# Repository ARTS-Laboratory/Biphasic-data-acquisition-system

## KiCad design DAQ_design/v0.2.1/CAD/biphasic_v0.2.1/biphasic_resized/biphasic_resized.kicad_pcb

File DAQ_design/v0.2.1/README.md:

# V0.2.1
All the files and soruce code developed by Borke at the University of Perugia

This version was transfered to KiCAD 7.0.2 and some changes where made. 

Added Arduino Nano interface and removed ATMega mandatories (clock, usb, etc.)

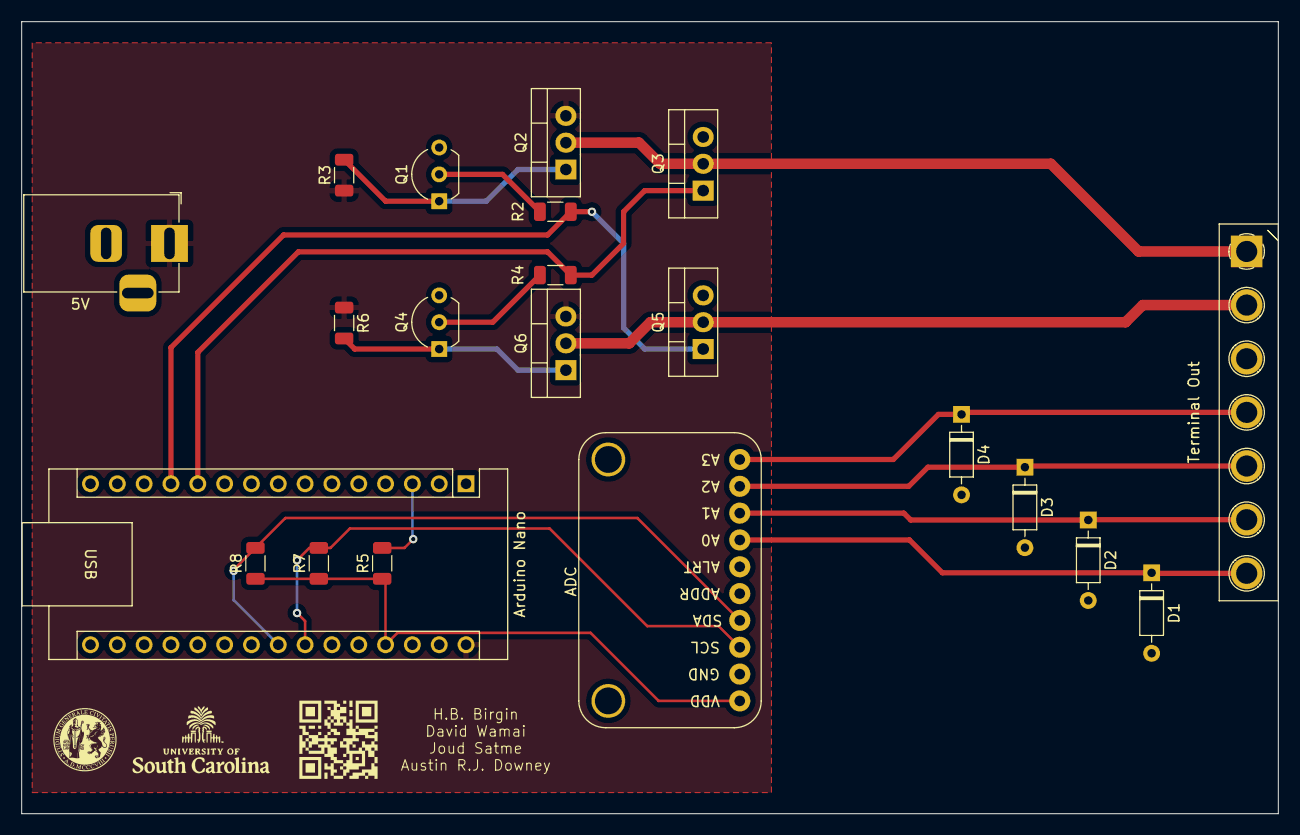
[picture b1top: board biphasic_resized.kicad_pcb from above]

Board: 2 copper layers, 119.0 x 75.0 mm, 25 parts (1 on the bottom side), 18 nets.

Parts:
5V: Barrel_Jack; BarrelJack_Horizontal
ADC: ADS1115IDGS; Adafruit_ADS1115
Arduino Nano: Arduino_Nano_Every; Arduino_Nano
D1, D2, D3, D4: D_Zener; D_DO-35_SOD27_P7.62mm_Horizontal
G2: LOGO; uofsc
G3: LOGO; upg
G5: LOGO; schematic
G7: LOGO; github
Q1, Q4: BC549; TO-92_Inline_Wide
Q2, Q6: IRF9540N; TO-220-3_Vertical
Q3, Q5: IRF540N; TO-220-3_Vertical
R2, R4: 1k; R_1206_3216Metric
R3, R5, R6, R7, R8: 10k; R_1206_3216Metric
Terminal Out: Screw_Terminal_01x07; TerminalBlock_Phoenix_MKDS-1,5-7-5.08_1x07_P5.08mm_Horizont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

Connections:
AIN0: ADC.7 (AIN0), D1.1 (K), Terminal Out.7
AIN1: ADC.8 (AIN1), D2.1 (K), Terminal Out.6
AIN2: ADC.9 (AIN2), D3.1 (K), Terminal Out.5
AIN3: ADC.10 (AIN3), D4.1 (K), Terminal Out.4
GND: 5V.2, ADC.2 (GND), ADC.5 (ADDR), Arduino Nano.4 (GND), Arduino Nano.29 (GND), D1.2 (A), D2.2 (A), D3.2 (A), D4.2 (A), Q1.3 (E), Q3.3 (S), Q4.3 (E), Q5.3 (S), Terminal Out.3
LOGIC1: Arduino Nano.12 (D9), Q5.1 (G), R2.2
LOGIC2: Arduino Nano.11 (D8), Q3.1 (G), R4.2
unnamed: ADC.3 (SCL), Arduino Nano.24 (SCL/A5), R7.2
unnamed: ADC.4 (SDA), Arduino Nano.23 (SDA/A4), R8.2
unnamed: Arduino Nano.3 (~RESET), R5.2
unnamed: Q1.2 (B), R2.1
unnamed: Q1.1 (C), Q2.1 (G), R3.2
unnamed: Q4.2 (B), R4.1
unnamed: Q4.1 (C), Q6.1 (G), R6.2
SN: Q5.2 (D), Q6.2 (D), Terminal Out.2
SP: Q2.2 (D), Q3.2 (D), Terminal Out.1
VDD: ADC.1 (VDD), Arduino Nano.27 (+5V), R5.1, R7.1, R8.1
VPP: 5V.1, Arduino Nano.30 (VIN), Q2.3 (S), Q6.3 (S), R3.1, R6.1

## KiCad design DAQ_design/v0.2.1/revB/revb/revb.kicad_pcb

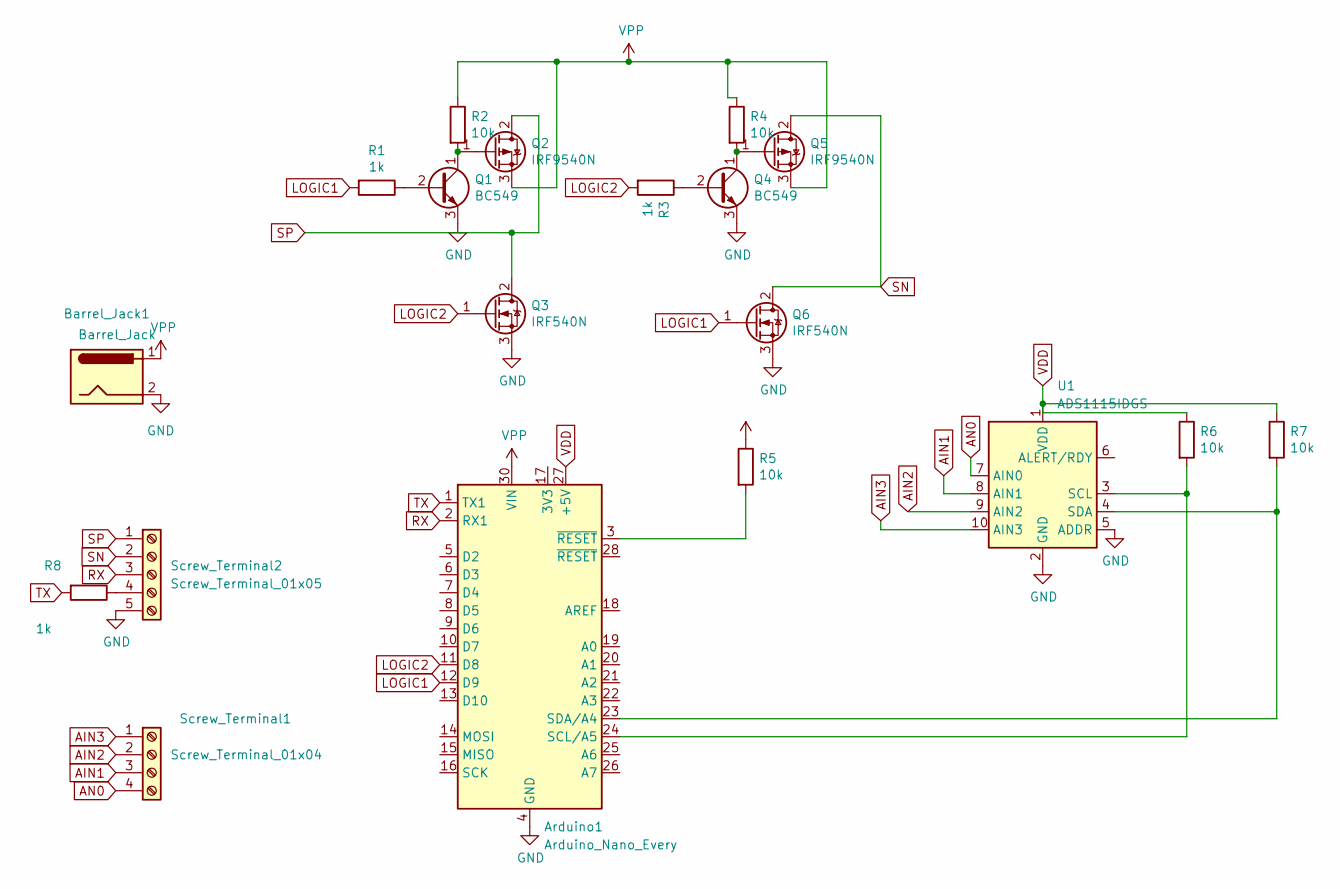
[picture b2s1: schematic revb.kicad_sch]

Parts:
Arduino1: Arduino_Nano_Every; Arduino_Nano_WithMountingHoles
Barrel_Jack1: Barrel_Jack; BarrelJack_Horizontal
Q1, Q4: BC549; TO-92_Inline_Wide
Q2, Q5: IRF9540N; TO-220-3_Vertical
Q3, Q6: IRF540N; TO-220-3_Vertical
R1, R3, R8: 1k; R_1206_3216Metric
R2, R4, R5, R6, R7: 10k; R_1206_3216Metric
Screw_Terminal1: Screw_Terminal_01x04; TerminalBlock_bornier-4_P5.08mm
Screw_Terminal2: Screw_Terminal_01x05; TerminalBlock_bornier-5_P5.08mm
U1: ADS1115IDGS; Adafruit_ADS1115

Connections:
AIN1: Screw_Terminal1.3, U1.8 (AIN1)
AIN2: Screw_Terminal1.2, U1.9 (AIN2)
AIN3: Screw_Terminal1.1, U1.10 (AIN3)
AN0: Screw_Terminal1.4, U1.7 (AIN0)
GND: Arduino1.4 (GND), Arduino1.29 (GND), Barrel_Jack1.2, Q1.3 (E), Q3.3 (S), Q4.3 (E), Q6.3 (S), Screw_Terminal2.5, U1.2 (GND), U1.5 (ADDR)
LOGIC1: Arduino1.12 (D9), Q6.1 (G), R1.2
LOGIC2: Arduino1.11 (D8), Q3.1 (G), R3.2
unnamed: Arduino1.24 (SCL/A5), R6.2, U1.3 (SCL)
unnamed: Arduino1.23 (SDA/A4), R7.2, U1.4 (SDA)
unnamed: Arduino1.3 (~RESET), R5.2
unnamed: Q1.2 (B), R1.1
unnamed: Q1.1 (C), Q2.1 (G), R2.2
unnamed: Q4.2 (B), R3.1
unnamed: Q4.1 (C), Q5.1 (G), R4.2
unnamed: R8.1, Screw_Terminal2.4
RX: Arduino1.2 (RX1), Screw_Terminal2.3
SN: Q5.2 (D), Q6.2 (D), Screw_Terminal2.2
SP: Q2.2 (D), Q3.2 (D), Screw_Terminal2.1
TX: Arduino1.1 (TX1), R8.2
VDD: Arduino1.27 (+5V), R5.1, R6.1, R7.1, U1.1 (VDD)
VPP: Arduino1.30 (VIN), Barrel_Jack1.1, Q2.3 (S), Q5.3 (S), R2.1, R4.1

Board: 2 copper layers, 23 parts (1 on the bottom side), 21 nets, no tracks yet.

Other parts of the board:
G2: LOGO; uofsc
G3: LOGO; upg
G5: LOGO; schematic
G7: LOGO; github

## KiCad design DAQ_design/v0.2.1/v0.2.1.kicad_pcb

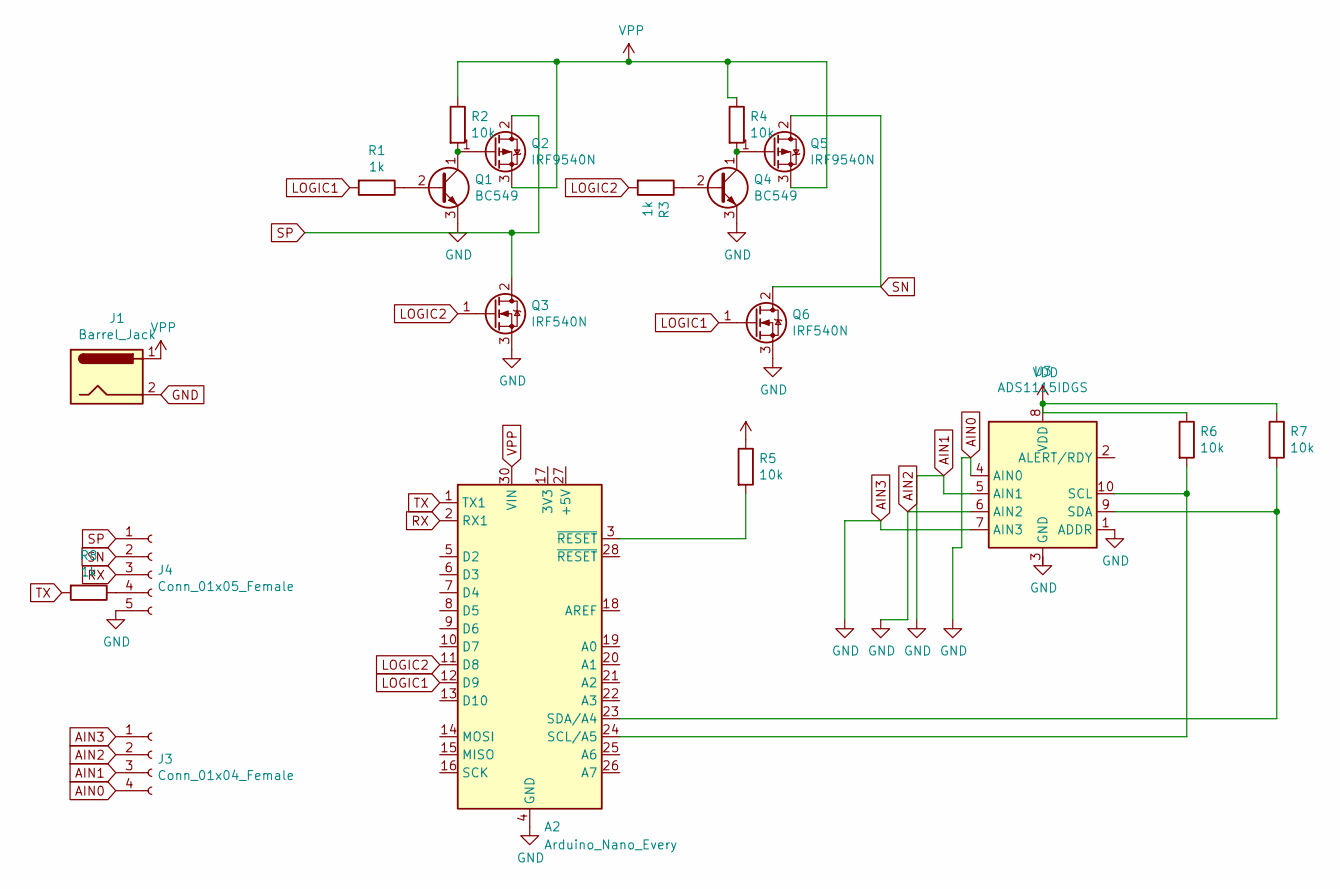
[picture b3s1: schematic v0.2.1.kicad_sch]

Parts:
A2: Arduino_Nano_Every; Arduino_Nano_WithMountingHoles
J1: Barrel_Jack; BarrelJack_Horizontal
J3: Conn_01x04_Female; PinSocket_1x04_P2.54mm_Vertical
J4: Conn_01x05_Female; PinSocket_1x05_P2.54mm_Vertical
Q1, Q4: BC549; TO-92_Inline_Wide
Q2, Q5: IRF9540N; TO-220-3_Vertical
Q3, Q6: IRF540N; TO-220-3_Vertical
R1, R3, R8: 1k; R_0603_1608Metric
R2, R4, R5, R6, R7: 10k; R_0603_1608Metric
U3: ADS1115IDGS; TSSOP-10_3x3mm_P0.5mm

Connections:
AIN0: A2.4 (GND), A2.29 (GND), J1.2, J3.1, J3.2, J3.3, J3.4, J4.5, Q1.3 (E), Q3.3 (S), Q4.3 (E), Q6.3 (S), U3.1 (ADDR), U3.4 (AIN0), U3.5 (AIN1), U3.6 (AIN2), U3.7 (AIN3)
LOGIC1: A2.12 (D9), Q6.1 (G), R1.2
LOGIC2: A2.11 (D8), Q3.1 (G), R3.2
unnamed: A2.24 (SCL/A5), R6.2, U3.10 (SCL)
unnamed: A2.23 (SDA/A4), R7.2, U3.9 (SDA)
unnamed: A2.3 (~RESET), R5.2
unnamed: J4.4, R8.1
unnamed: Q1.2 (B), R1.1
unnamed: Q1.1 (C), Q2.1 (G), R2.2
unnamed: Q4.2 (B), R3.1
unnamed: Q4.1 (C), Q5.1 (G), R4.2
RX: A2.2 (RX1), J4.3
SN: J4.2, Q5.2 (D), Q6.2 (D)
SP: J4.1, Q2.2 (D), Q3.2 (D)
TX: A2.1 (TX1), R8.2
VDD: R5.1, R6.1, R7.1, U3.8 (VDD)
VPP: A2.30 (VIN), J1.1, Q2.3 (S), Q5.3 (S), R2.1, R4.1

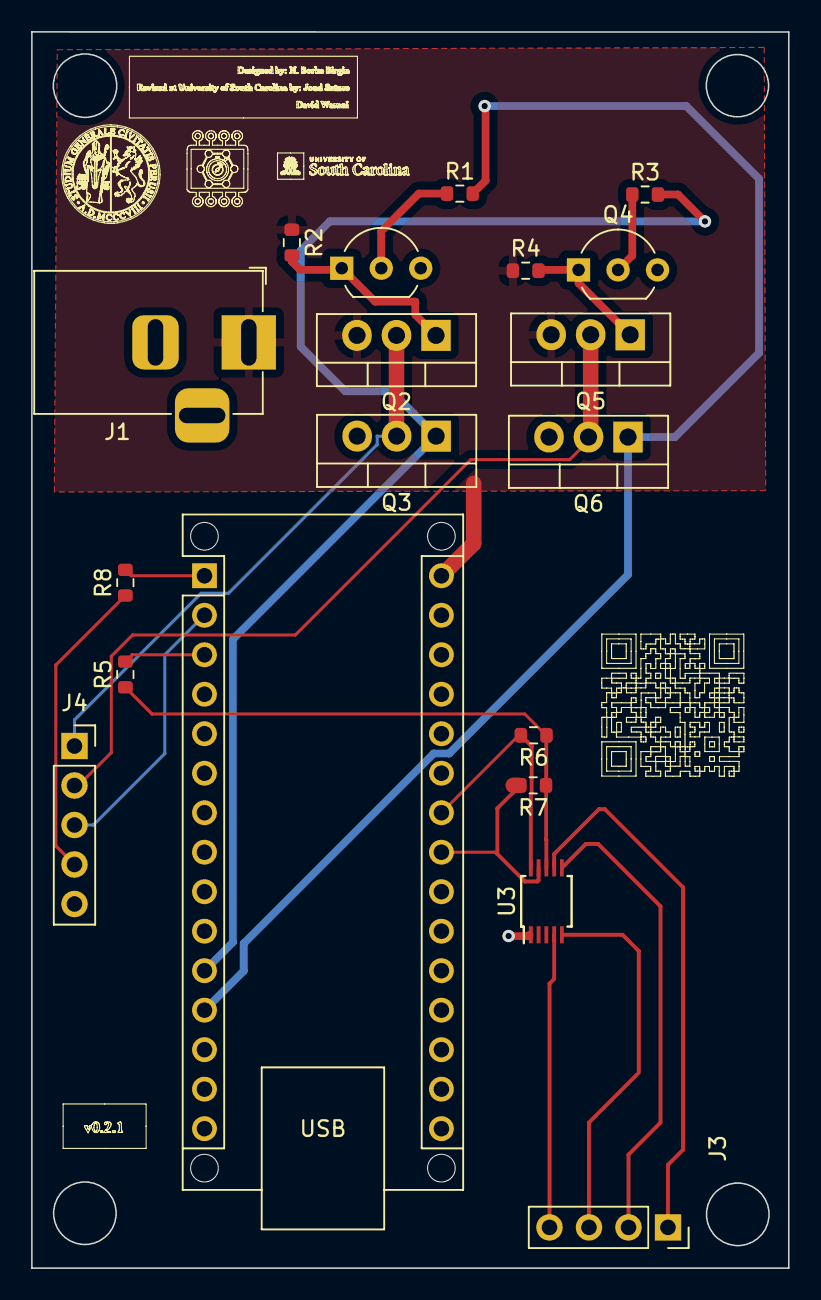
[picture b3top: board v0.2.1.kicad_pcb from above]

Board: 2 copper layers, 48.7 x 79.5 mm, 19 parts (0 on the bottom side), 17 nets.
